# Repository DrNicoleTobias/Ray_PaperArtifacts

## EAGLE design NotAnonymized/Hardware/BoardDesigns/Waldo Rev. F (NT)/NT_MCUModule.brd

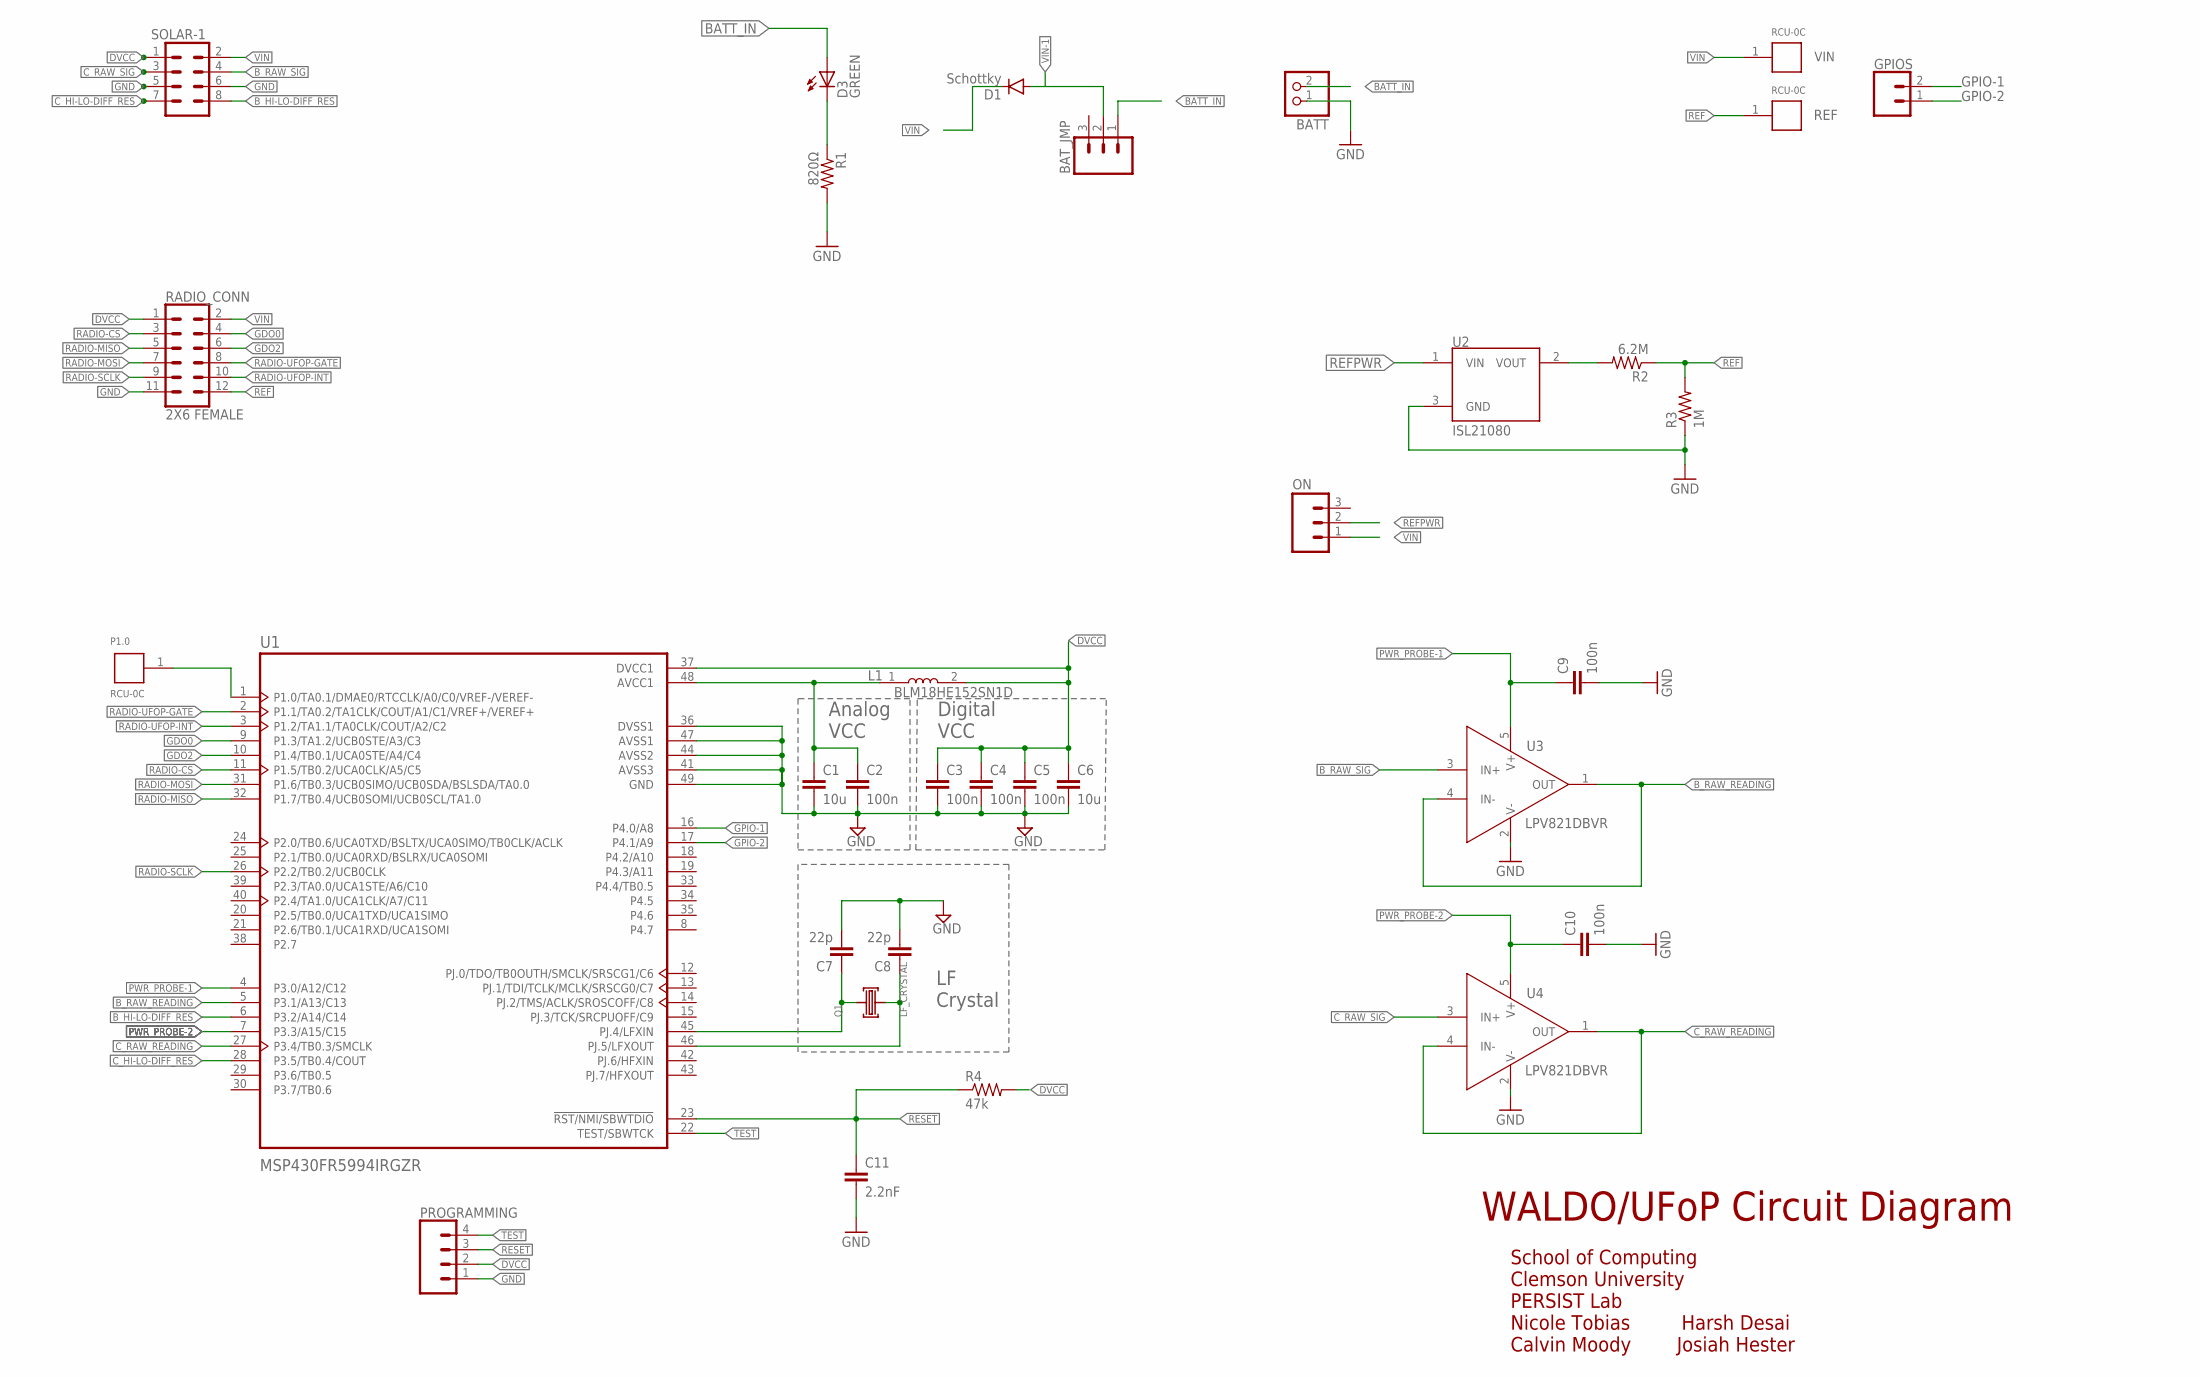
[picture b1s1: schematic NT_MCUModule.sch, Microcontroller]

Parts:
BATT: PINHD-1X2; 1X02
BAT_JMP: M03; 1X03-1.27MM
C1, C6: 10u; C0603
C2, C3, C4, C5, C9, C10: 100n; C0603
C7, C8: 22p; C0603
C11: 2.2nF; C0603
D1: Schottky; SOD523
D3: GREEN; CHIP-LED0805
GPIOS: CONN_02; 1X02
L1: BLM18HE152SN1D; INDC1608X95
ON: M03; 1X03-1.27MM
P1.0: RCU-0C; TE_RCU-0C
PROGRAMMING: CONN_04; 1X04
Q1: LF_CRYSTAL
R1: 820Ω; 0603-RES
R2: 6.2M; 0603-RES; DIGIKEY 541-6.20MHCT-ND
R3: 1M; 0603-RES; DIGIKEY 311-1.00MHRCT-ND
R4: 47k; 0603-RES; DIGIKEY 311-1.00MHRCT-ND
RADIO_CONN: 2X6 FEMALE; 2X6
REF: RCU-0C; TE_RCU-0C
SOLAR-1: CONN_04X2; 2X4
U1: MSP430FR5994IRGZR; QFN50P700X700X100-49N
U2: ISL21080; SOT-23; DIGIKEY ISL21080DIH309Z-TKCT-ND
U3, U4: LPV821DBVR; SOT95P280X145-5N
VIN: RCU-0C; TE_RCU-0C

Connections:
AVCC: C1.1, C2.1, L1.1, U1.48 (AVCC1)
BATT_IN: BATT.2, BAT_JMP.1, D3.A
B_HI-LO-DIFF_RES: SOLAR-1.8, U1.6 (P3.2/A14/C14)
B_RAW_READING: U1.5 (P3.1/A13/C13), U3.1 (OUT), U3.4 (IN-)
B_RAW_SIG: SOLAR-1.4, U3.3 (IN+)
C_HI-LO-DIFF_RES: SOLAR-1.7, U1.28 (P3.5/TB0.4/COUT)
C_RAW_READING: U1.27 (P3.4/TB0.3/SMCLK), U4.1 (OUT), U4.4 (IN-)
C_RAW_SIG: SOLAR-1.3, U4.3 (IN+)
DVCC: C3.1, C4.1, C5.1, C6.1, L1.2, PROGRAMMING.2, R4.2, RADIO_CONN.1, SOLAR-1.1, U1.37 (DVCC1)
GDO0: RADIO_CONN.4, U1.9 (P1.3/TA1.2/UCB0STE/A3/C3)
GDO2: RADIO_CONN.6, U1.10 (P1.4/TB0.1/UCA0STE/A4/C4)
GND: BATT.1, C1.2, C2.2, C3.2, C4.2, C5.2, C6.2, C7.2, C8.2, C9.2, C10.2, C11.2, PROGRAMMING.1, R1.2, R3.1, RADIO_CONN.11, SOLAR-1.5, SOLAR-1.6, U1.36 (DVSS1), U1.41 (AVSS3), U1.44 (AVSS2), U1.47 (AVSS1), U1.49 (GND), U2.3 (GND), U3.2 (V-), U4.2 (V-)
GPIO-1: GPIOS.2, U1.16 (P4.0/A8)
GPIO-2: GPIOS.1, U1.17 (P4.1/A9)
unnamed: P1.0.1, U1.1 (P1.0/TA0.1/DMAE0/RTCCLK/A0/C0/VREF-/VER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)
unnamed: D3.C, R1.1
unnamed: R2.2, U2.2 (VOUT)
unnamed: C8.1, Q1.2, U1.46 (PJ.5/LFXOUT)
unnamed: C7.1, Q1.1, U1.45 (PJ.4/LFXIN)
PWR_PROBE-1: C9.1, U1.4 (P3.0/A12/C12), U3.5 (V+)
PWR_PROBE-2: C10.1, U1.7 (P3.3/A15/C15), U4.5 (V+)
RADIO-CS: RADIO_CONN.3, U1.11 (P1.5/TB0.2/UCA0CLK/A5/C5)
RADIO-MISO: RADIO_CONN.5, U1.32 (P1.7/TB0.4/UCB0SOMI/UCB0SCL/TA1.0)
RADIO-MOSI: RADIO_CONN.7, U1.31 (P1.6/TB0.3/UCB0SIMO/UCB0SDA/BSLSDA/TA0.0)
RADIO-SCLK: RADIO_CONN.9, U1.26 (P2.2/TB0.2/UCB0CLK)
RADIO-UFOP-GATE: RADIO_CONN.8, U1.2 (P1.1/TA0.2/TA1CLK/COUT/A1/C1/VREF+/VERE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)
RADIO-UFOP-INT: RADIO_CONN.10, U1.3 (P1.2/TA1.1/TA0CLK/COUT/A2/C2)
REF: R2.1, R3.2, RADIO_CONN.12, REF.1
REFPWR: ON.2, U2.1 (VIN)
RESET: C11.1, PROGRAMMING.3, R4.1, U1.23 (!RST/NMI/SBWTDIO)
TEST: PROGRAMMING.4, U1.22 (TEST/SBWTCK)
VIN: D1.C, ON.1, RADIO_CONN.2, SOLAR-1.2, VIN.1
VIN-1: BAT_JMP.2, D1.A

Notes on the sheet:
WALDO/UFoP Circuit Diagram
School of Computing Clemson University PERSIST Lab Nicole Tobias Harsh Desai Calvin Moody Josiah Hester
Analog
VCC
Digital
Crystal

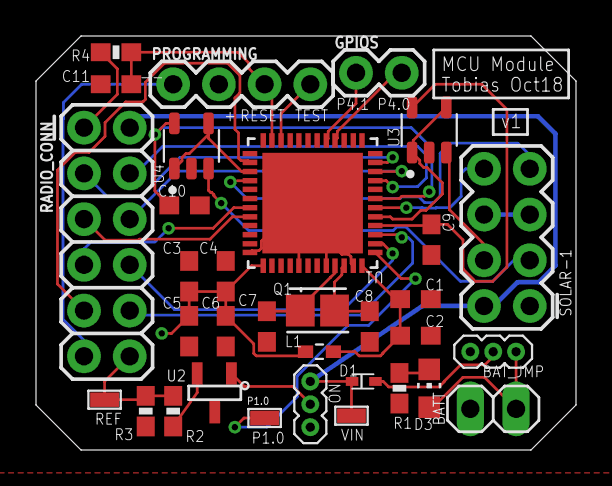
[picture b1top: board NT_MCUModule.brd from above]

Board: 2 copper layers, 30.0 x 23.0 mm, 33 parts (0 on the bottom side), 33 nets.

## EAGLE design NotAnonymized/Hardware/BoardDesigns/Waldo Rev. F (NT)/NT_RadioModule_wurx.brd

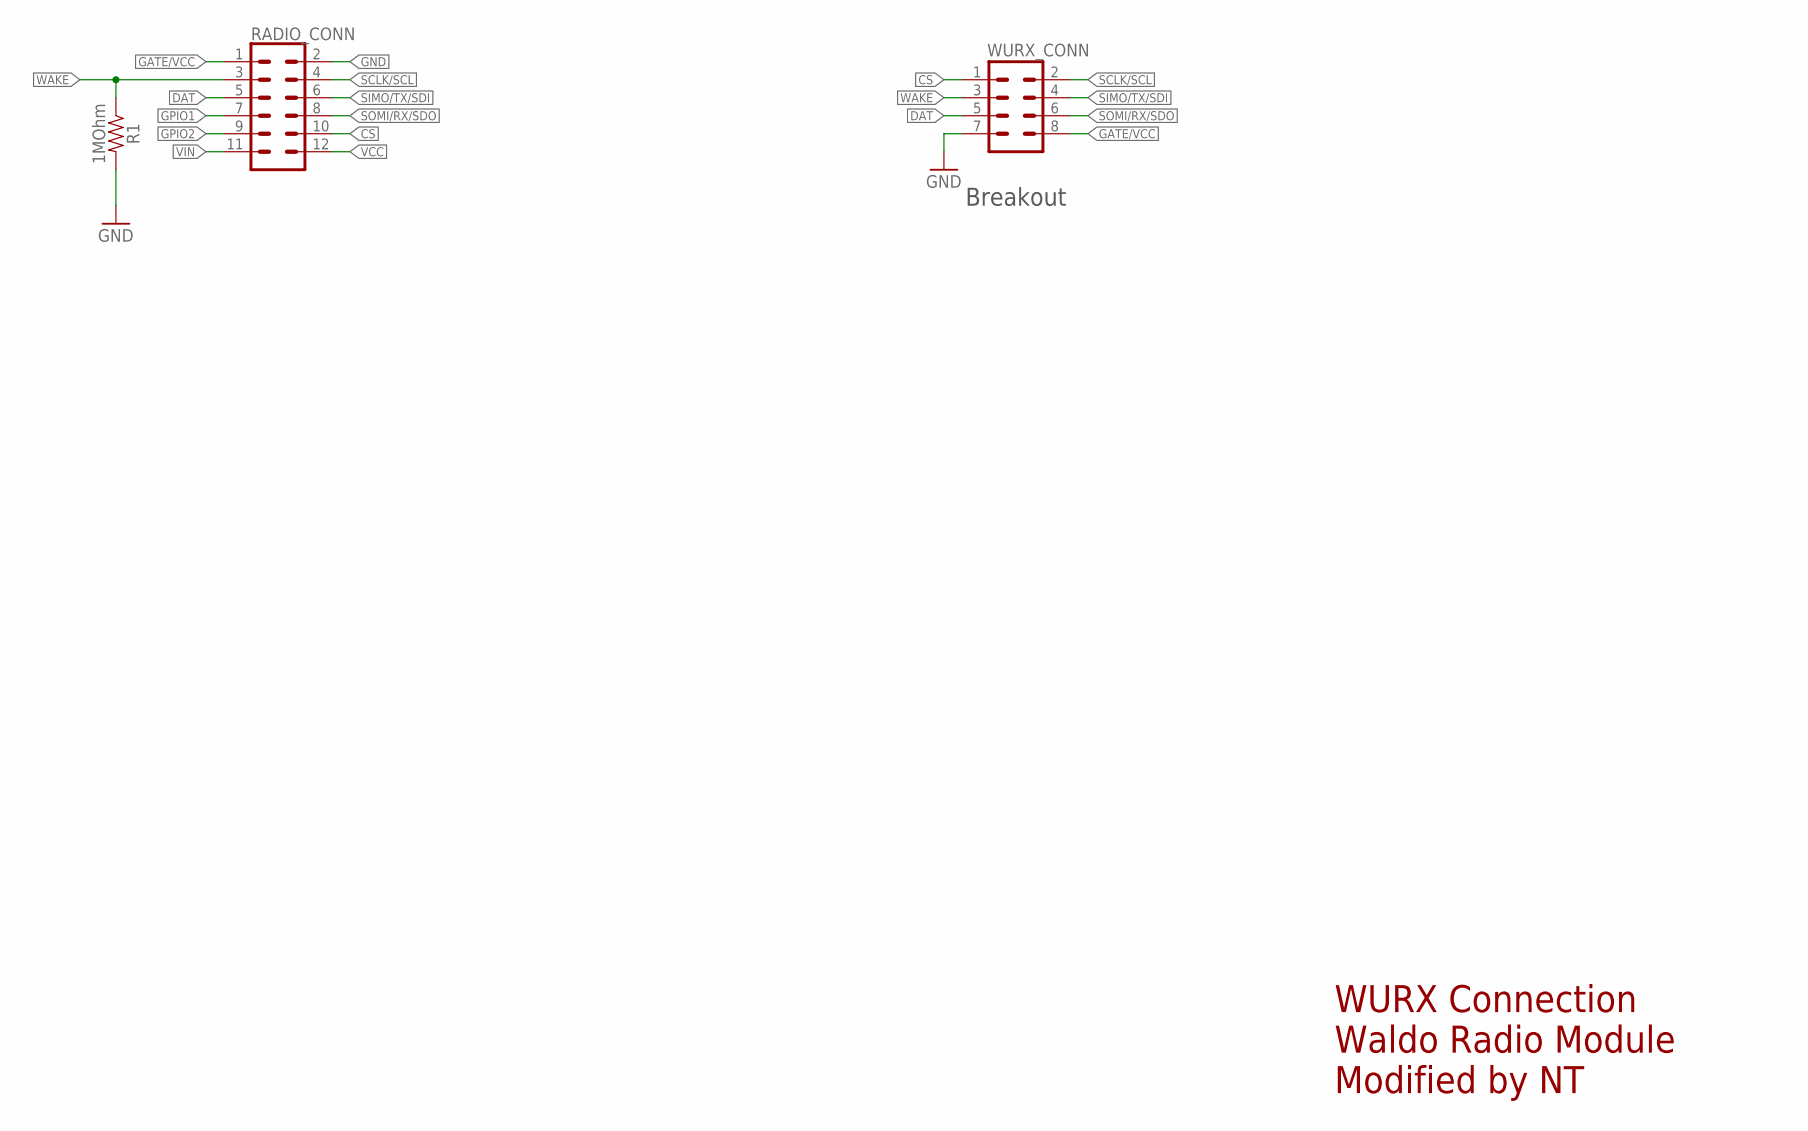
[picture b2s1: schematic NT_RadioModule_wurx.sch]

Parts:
R1: 1MOhm; 0805
RADIO_CONN: CONN_06X2PTH_FEMALE; 2X6
WURX_CONN: M04X2; 2X4

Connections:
CS: RADIO_CONN.10, WURX_CONN.1
DAT: RADIO_CONN.5, WURX_CONN.5
GATE/VCC: RADIO_CONN.1, WURX_CONN.8
GND: R1.2, RADIO_CONN.2, WURX_CONN.7
GPIO1: RADIO_CONN.7
GPIO2: RADIO_CONN.9
SCLK/SCL: RADIO_CONN.4, WURX_CONN.2
SIMO/TX/SDI: RADIO_CONN.6, WURX_CONN.4
SOMI/RX/SDO: RADIO_CONN.8, WURX_CONN.6
VCC: RADIO_CONN.12
VIN: RADIO_CONN.11
WAKE: R1.1, RADIO_CONN.3, WURX_CONN.3

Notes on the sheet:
WURX Connection Waldo Radio Module Modified by NT
Breakout

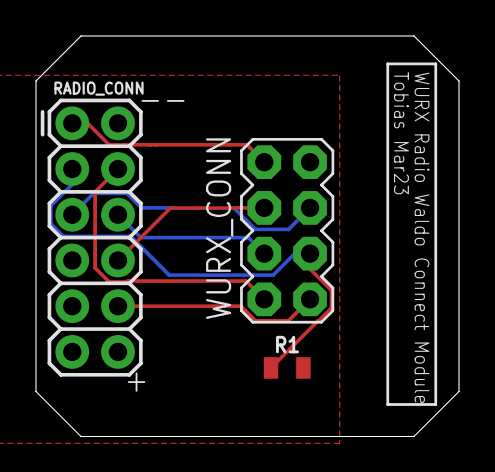
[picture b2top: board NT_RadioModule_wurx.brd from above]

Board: 2 copper layers, 23.5 x 22.2 mm, 3 parts (0 on the bottom side), 8 nets.

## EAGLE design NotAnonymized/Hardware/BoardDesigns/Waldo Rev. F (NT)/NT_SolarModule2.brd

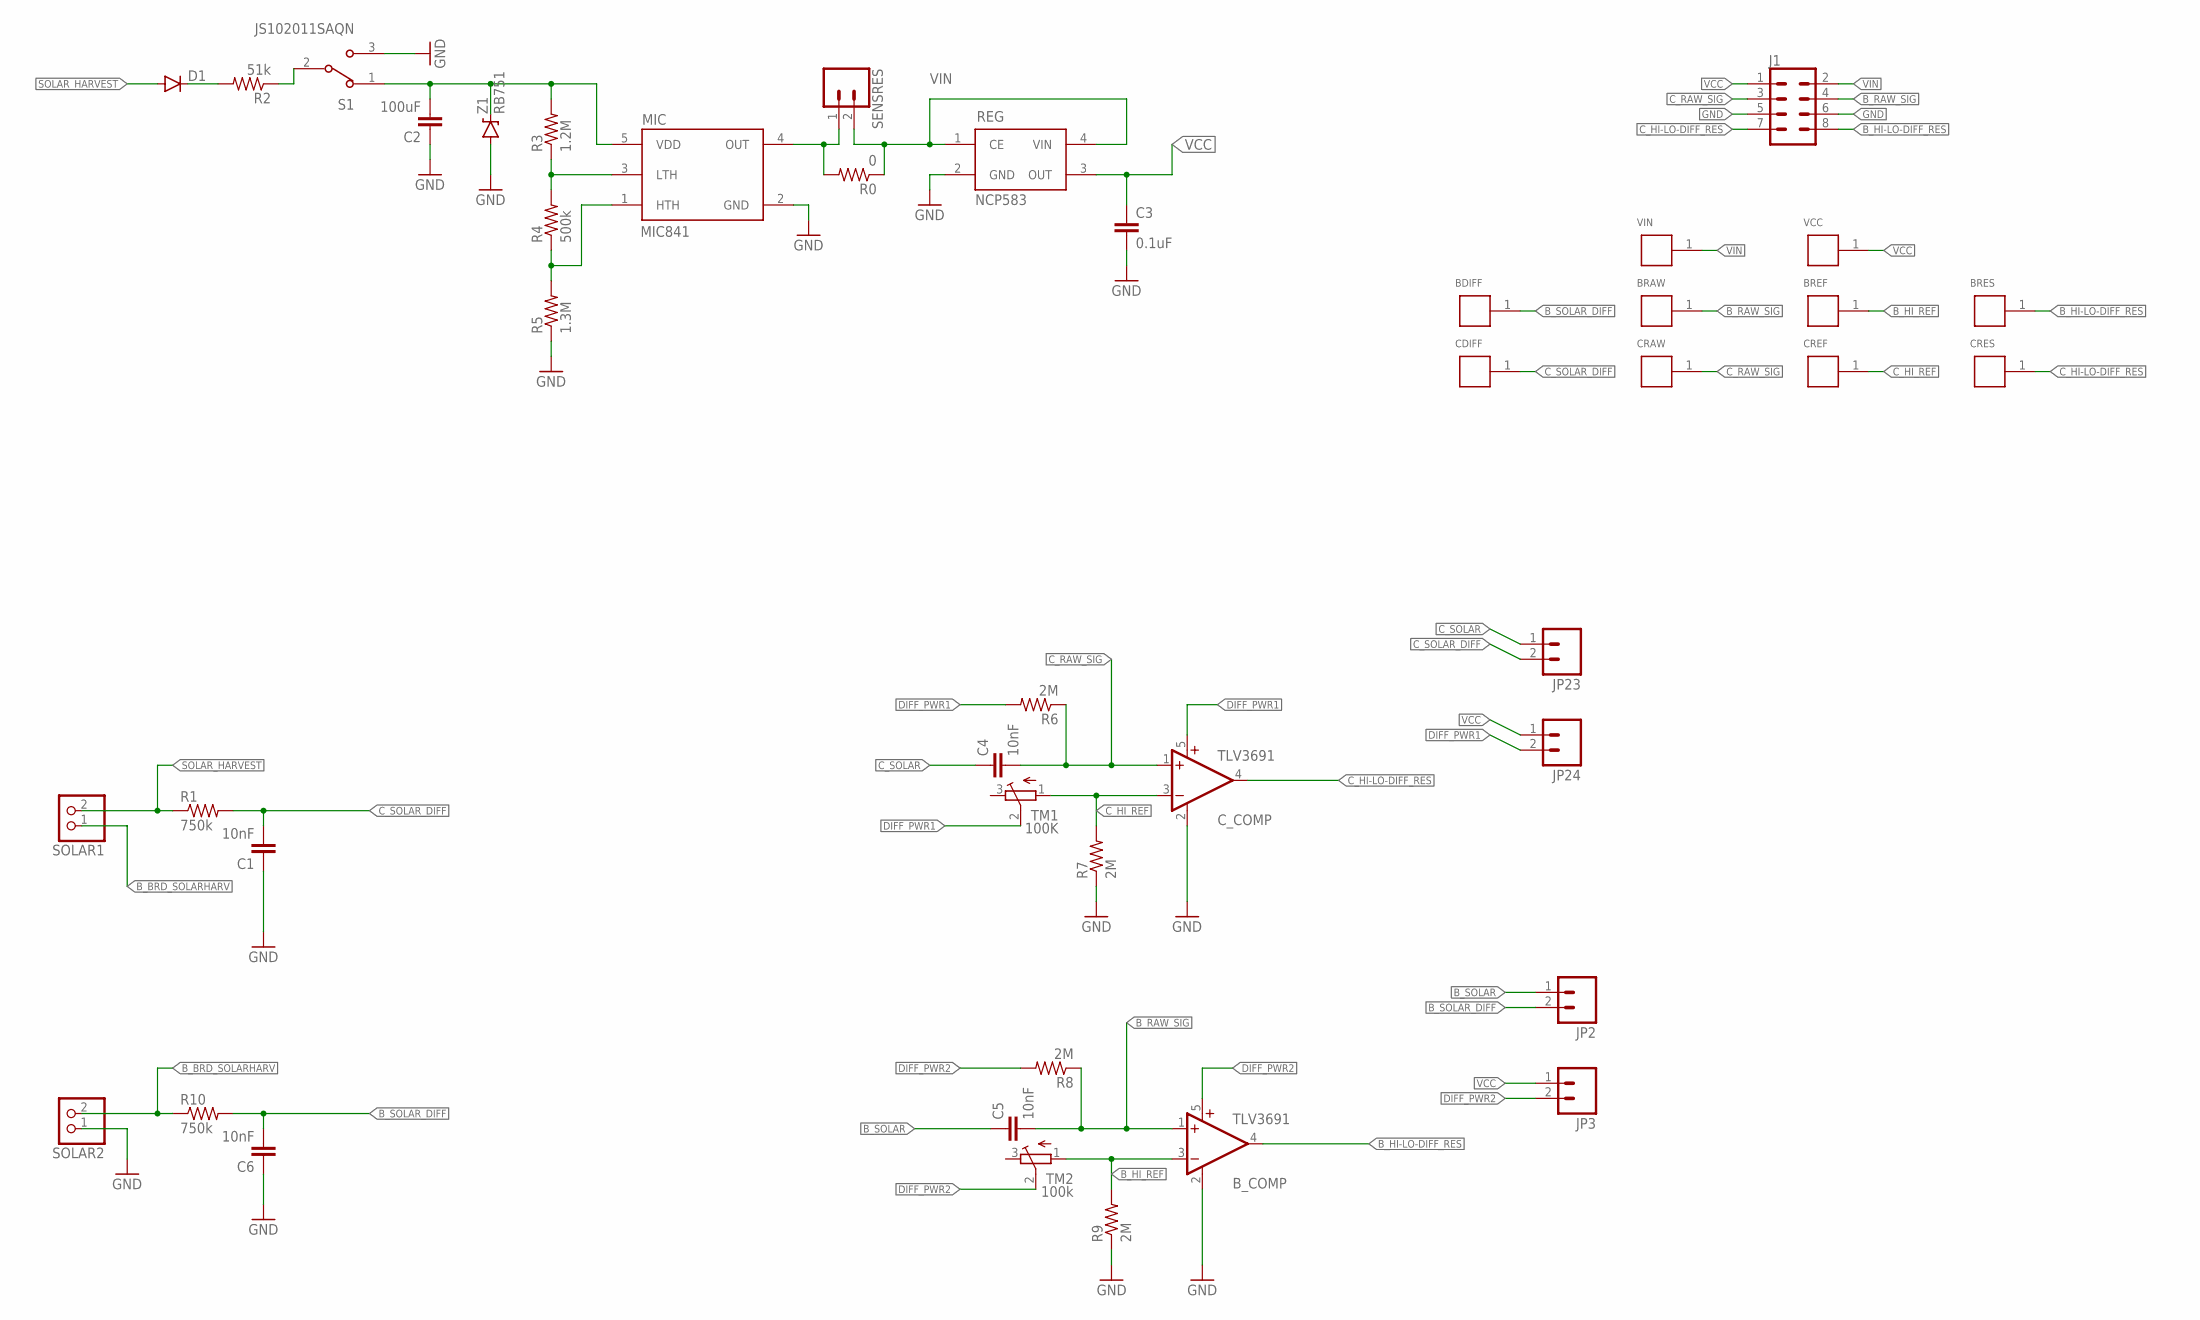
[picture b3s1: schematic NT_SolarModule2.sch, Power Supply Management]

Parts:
BDIFF: RCU-0C; TE_RCU-0C
BRAW: RCU-0C; TE_RCU-0C
BREF: RCU-0C; TE_RCU-0C
BRES: RCU-0C; TE_RCU-0C
B_COMP: TLV3691; SC70-5
C1, C4, C5, C6: 10nF; 0603-CAP
C2: 100uF; 0603-CAP
C3: 0.1uF; 0603-CAP
CDIFF: RCU-0C; TE_RCU-0C
CRAW: RCU-0C; TE_RCU-0C
CREF: RCU-0C; TE_RCU-0C
CRES: RCU-0C; TE_RCU-0C
C_COMP: TLV3691; SC70-5
D1: DIODESOD523; SOD523
J1: CONN_04X2; 2X4
JP2, JP3, JP23, JP24: M02; 1X02-1.27MM
MIC: MIC841; SC70-5
R0: 0; 0603-RES
R1, R10: 750k; 0603-RES
R2: 51k; 0603-RES
R3: 1.2M; 0603-RES
R4: 500k; 0603-RES
R5: 1.3M; 0603-RES
R6, R7, R8, R9: 2M; 0603-RES
REG: NCP583; SC82-AB_1PRIMARY
S1: JS102011SAQN; SW_JS102011SAQN
SENSRES: CONN_02; 1X02
SOLAR1, SOLAR2: PINHD-1X2; 1X02
TM1: 100K; TC33X
TM2: 100k; TC33X
VCC: RCU-0C; TE_RCU-0C
VIN: RCU-0C; TE_RCU-0C
Z1: RB751; SOD-523

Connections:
B_BRD_SOLARHARV: R10.1, SOLAR1.1, SOLAR2.2
B_HI-LO-DIFF_RES: BRES.1, B_COMP.4 (OUT), J1.8
B_HI_REF: BREF.1, B_COMP.3 (-IN), R9.2, TM2.1 (A)
B_RAW_SIG: BRAW.1, B_COMP.1 (+IN), C5.2, J1.4, R8.1
B_SOLAR: C5.1, JP2.1
B_SOLAR_DIFF: BDIFF.1, C6.2, JP2.2, R10.2
C_HI-LO-DIFF_RES: CRES.1, C_COMP.4 (OUT), J1.7
C_HI_REF: CREF.1, C_COMP.3 (-IN), R7.2, TM1.1 (A)
C_RAW_SIG: C4.2, CRAW.1, C_COMP.1 (+IN), J1.3, R6.1
C_SOLAR: C4.1, JP23.1
C_SOLAR_DIFF: C1.2, CDIFF.1, JP23.2, R1.2
DIFF_PWR1: C_COMP.5 (V+), JP24.2, R6.2, TM1.2 (S)
DIFF_PWR2: B_COMP.5 (V+), JP3.2, R8.2, TM2.2 (S)
GND: B_COMP.2 (GND), C1.1, C2.1, C3.2, C6.1, C_COMP.2 (GND), J1.5, J1.6, MIC.2 (GND), R5.1, R7.1, R9.1, REG.2 (GND), S1.3, SOLAR2.1, Z1.ANODE (A)
MIC_INPUT: C2.2, MIC.5 (VDD), R3.2, S1.1, Z1.CATHODE (C)
unnamed: D1.C, R2.2
unnamed: MIC.4 (OUT), R0.2, SENSRES.1
unnamed: R2.1, S1.2
unnamed: MIC.3 (LTH), R3.1, R4.2
unnamed: MIC.1 (HTH), R4.1, R5.2
SOLAR_HARVEST: D1.A, R1.1, SOLAR1.2
VCC: C3.1, J1.1, JP3.1, JP24.1, REG.3 (OUT), VCC.1
VIN: J1.2, R0.1, REG.1 (CE), REG.4 (VIN), SENSRES.2, VIN.1

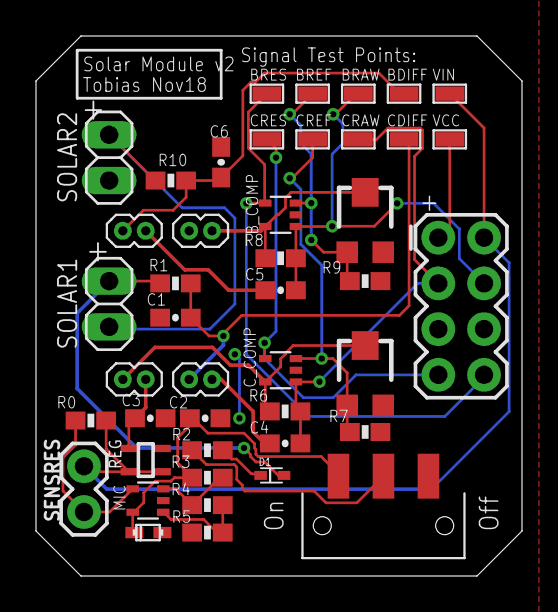
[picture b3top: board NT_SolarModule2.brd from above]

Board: 2 copper layers, 27.0 x 30.0 mm, 44 parts (0 on the bottom side), 23 nets.

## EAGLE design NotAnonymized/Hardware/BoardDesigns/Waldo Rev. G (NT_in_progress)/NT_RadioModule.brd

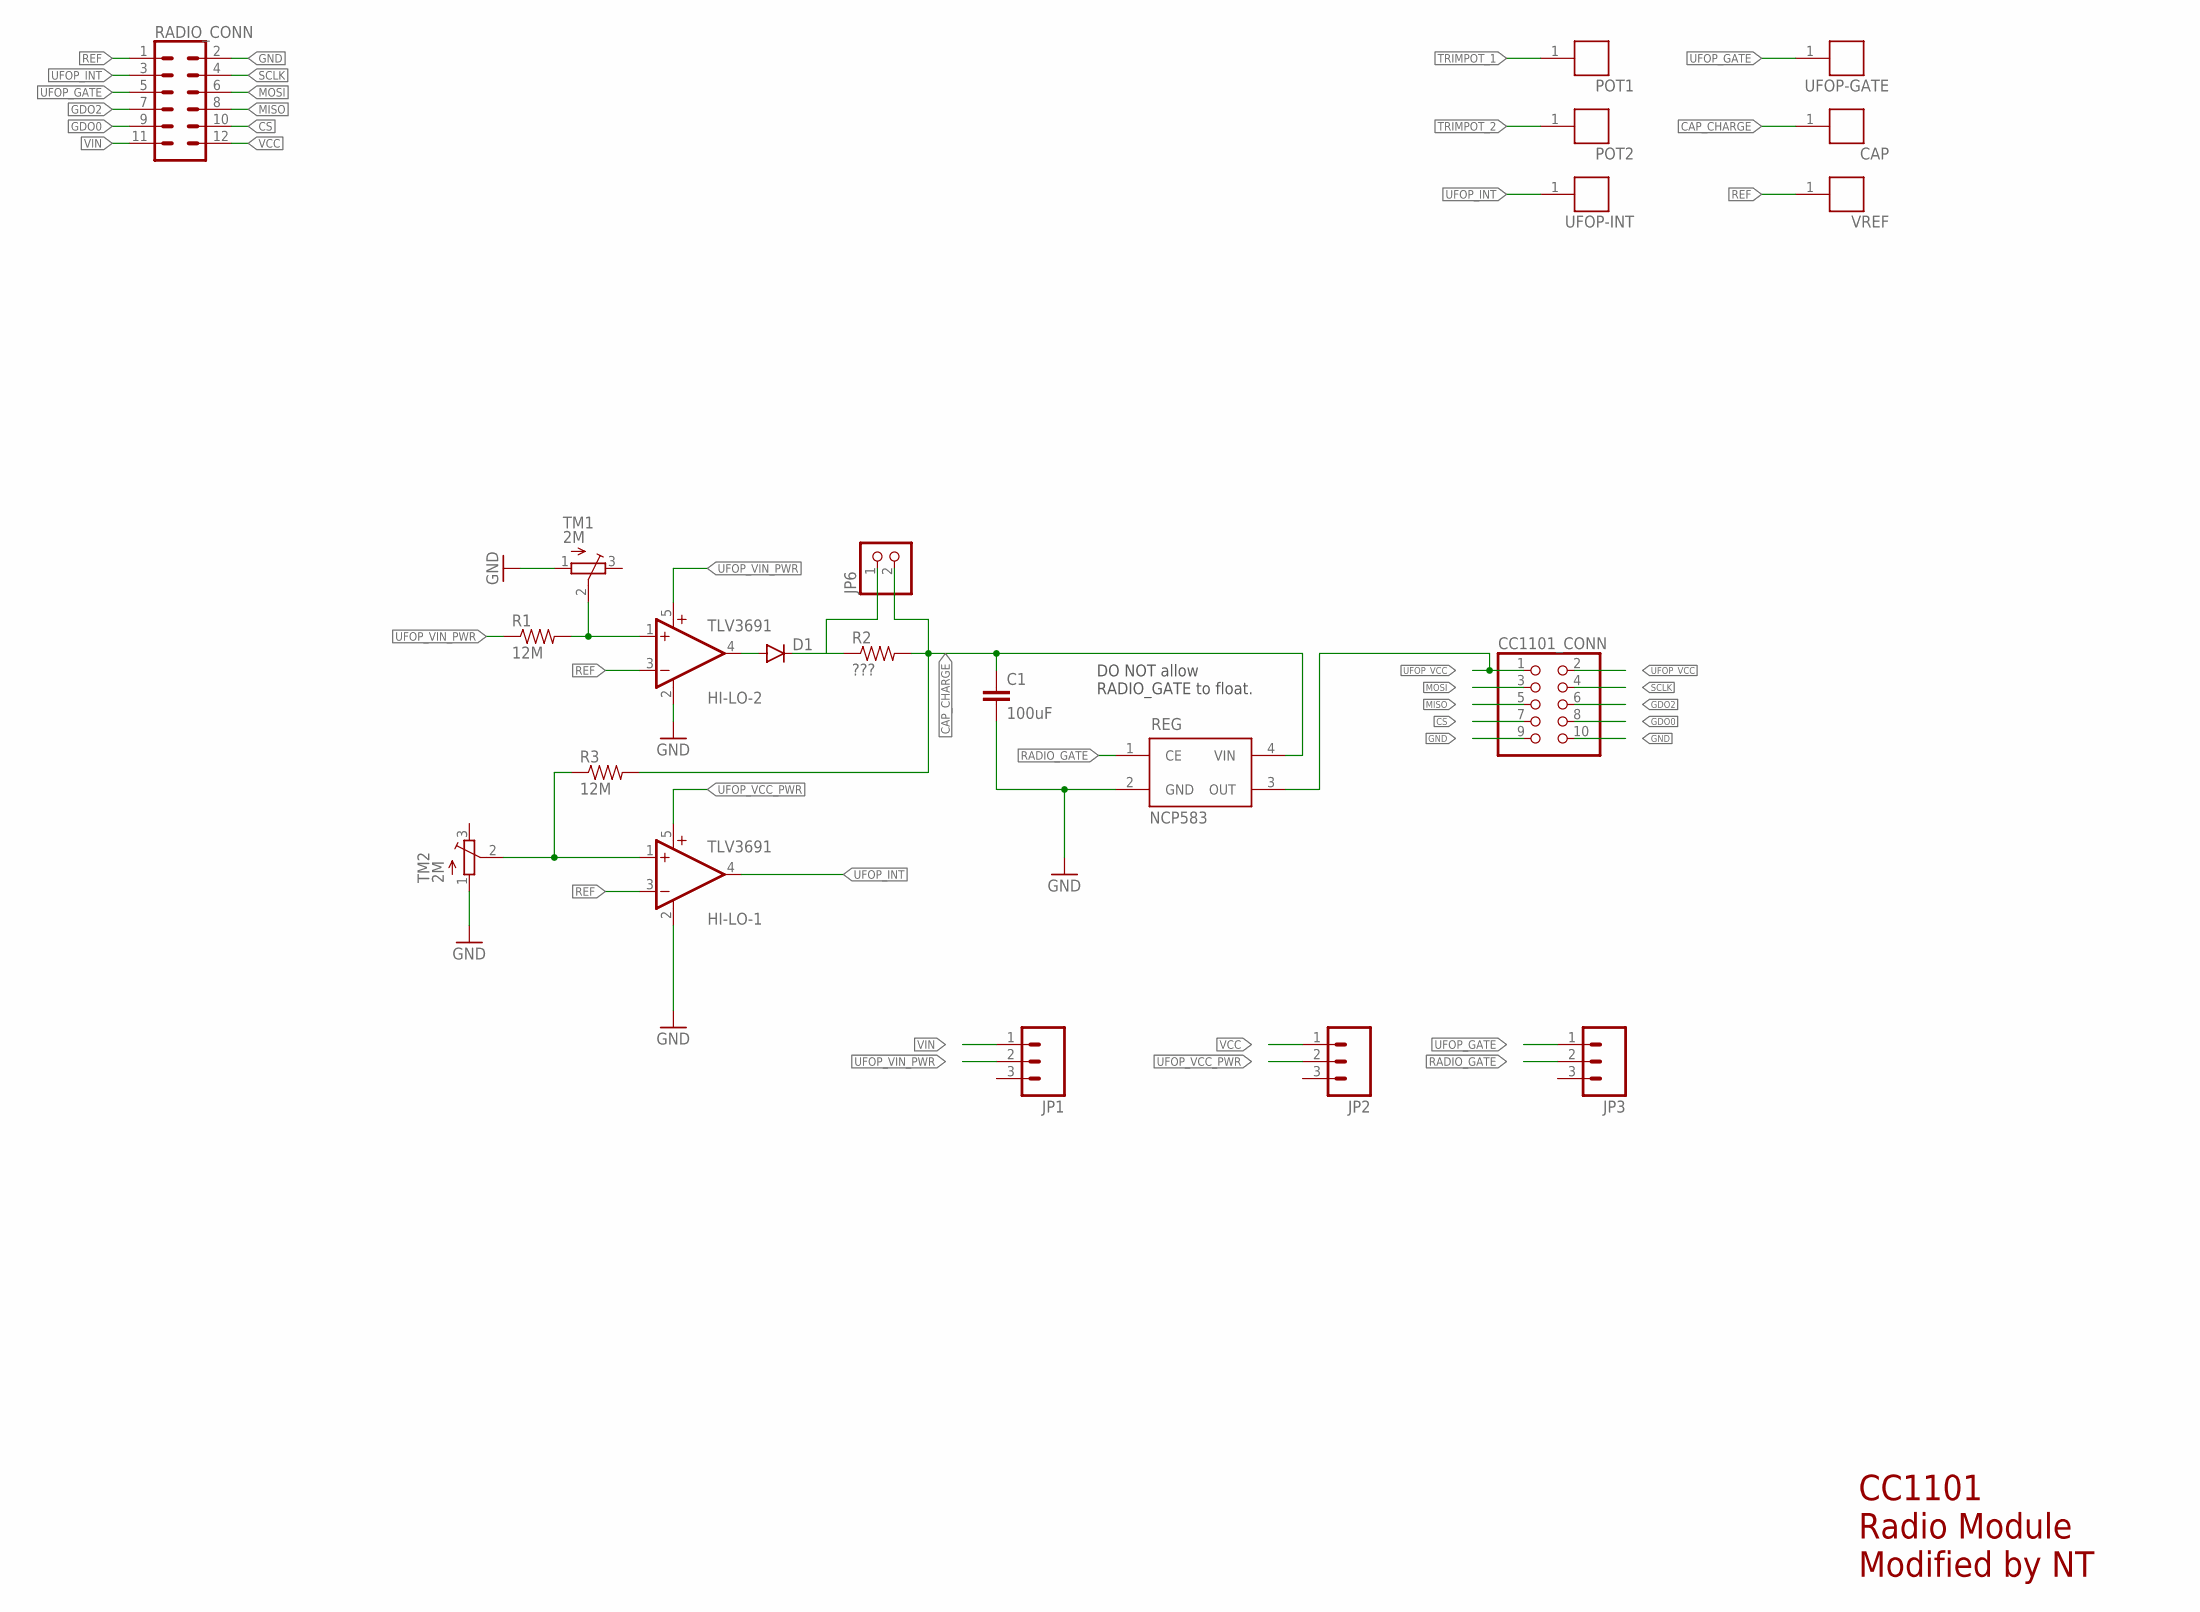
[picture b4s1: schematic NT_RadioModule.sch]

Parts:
C1: 100uF; 0603-CAP; DIGIKEY 490-9969-1-ND
CAP: RCU-0C; TE_RCU-0C
CC1101_CONN: PINHD-2X5; 2X05
D1: DIODESOD523; SOD523
HI-LO-1, HI-LO-2: TLV3691; SC70-5
JP1, JP2, JP3: M03; 1X03-1.27MM
JP6: PINHD-1X2; 1X02
POT1, POT2: RCU-0C; TE_RCU-0C
R1: 12M; 0603-RES
R2: ???; 0603-RES; DIGIKEY 311-2.00MHRCT-ND
R3: 12M; 0603-RES; DIGIKEY 311-2.00MHRCT-ND
RADIO_CONN: CONN_06X2PTH_FEMALE; 2X6
REG: NCP583; SC82-AB_1PRIMARY
TM1, TM2: 2M; TC33X
UFOP-GATE: RCU-0C; TE_RCU-0C
UFOP-INT: RCU-0C; TE_RCU-0C
VREF: RCU-0C; TE_RCU-0C

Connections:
CAP_CHARGE: C1.1, CAP.1, JP6.2, R2.2, R3.2, REG.4 (VIN)
CS: CC1101_CONN.7, RADIO_CONN.10
GDO0: CC1101_CONN.8, RADIO_CONN.9
GDO2: CC1101_CONN.6, RADIO_CONN.7
GND: C1.2, CC1101_CONN.9, CC1101_CONN.10, HI-LO-1.2 (GND), HI-LO-2.2 (GND), RADIO_CONN.2, REG.2 (GND), TM1.1 (A), TM2.1 (A)
MISO: CC1101_CONN.5, RADIO_CONN.8
MOSI: CC1101_CONN.3, RADIO_CONN.6
unnamed: D1.C, JP6.1, R2.1
unnamed: D1.A, HI-LO-2.4 (OUT)
RADIO_GATE: JP3.2, REG.1 (CE)
REF: HI-LO-1.3 (-IN), HI-LO-2.3 (-IN), RADIO_CONN.1, VREF.1
SCLK: CC1101_CONN.4, RADIO_CONN.4
TRIMPOT_1: HI-LO-2.1 (+IN), POT1.1, R1.2, TM1.2 (S)
TRIMPOT_2: HI-LO-1.1 (+IN), POT2.1, R3.1, TM2.2 (S)
UFOP_GATE: JP3.1, RADIO_CONN.5, UFOP-GATE.1
UFOP_INT: HI-LO-1.4 (OUT), RADIO_CONN.3, UFOP-INT.1
UFOP_VCC: CC1101_CONN.1, CC1101_CONN.2, REG.3 (OUT)
UFOP_VCC_PWR: HI-LO-1.5 (V+), JP2.2
UFOP_VIN_PWR: HI-LO-2.5 (V+), JP1.2, R1.1
VCC: JP2.1, RADIO_CONN.12
VIN: JP1.1, RADIO_CONN.11

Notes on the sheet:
CC1101 Radio Module Modified by NT
DO NOT allow RADIO_GATE to float.

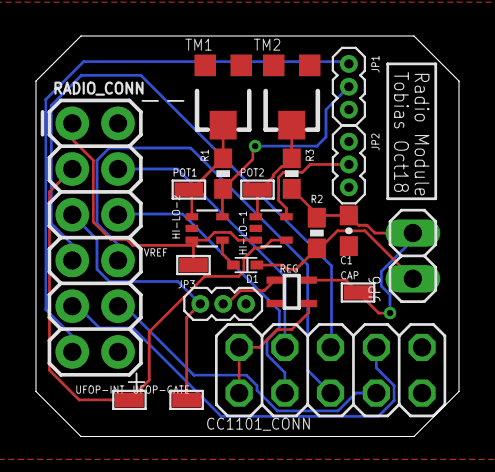
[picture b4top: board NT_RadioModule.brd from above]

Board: 2 copper layers, 23.5 x 22.2 mm, 22 parts (0 on the bottom side), 21 nets.

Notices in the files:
parts and their libraries:
SparkFun-Connectors: Licensing: Creative Commons ShareAlike 4.0 International - https://creativecommons.org/licenses/by-sa/4.0
